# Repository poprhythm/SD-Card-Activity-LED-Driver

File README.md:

# SD-Card-Activity-LED-Driver
Switches on and off an LED based on SD Card activity

Components

- C1:	0.1uF	 SMD 0805
- D1:	LED	SMD 0201
- Q1: [BSS138](https://www.onsemi.com/pub/Collateral/BSS138-D.PDF)
- R1:	2K	SMD 0805
- R2:	330	SMD 0805
- U1:	[74LVC1G04](https://www.ti.com/product/SN74LVC1G04)
- Conn_LDO: AMS1117-3.3V Buck Module LDO

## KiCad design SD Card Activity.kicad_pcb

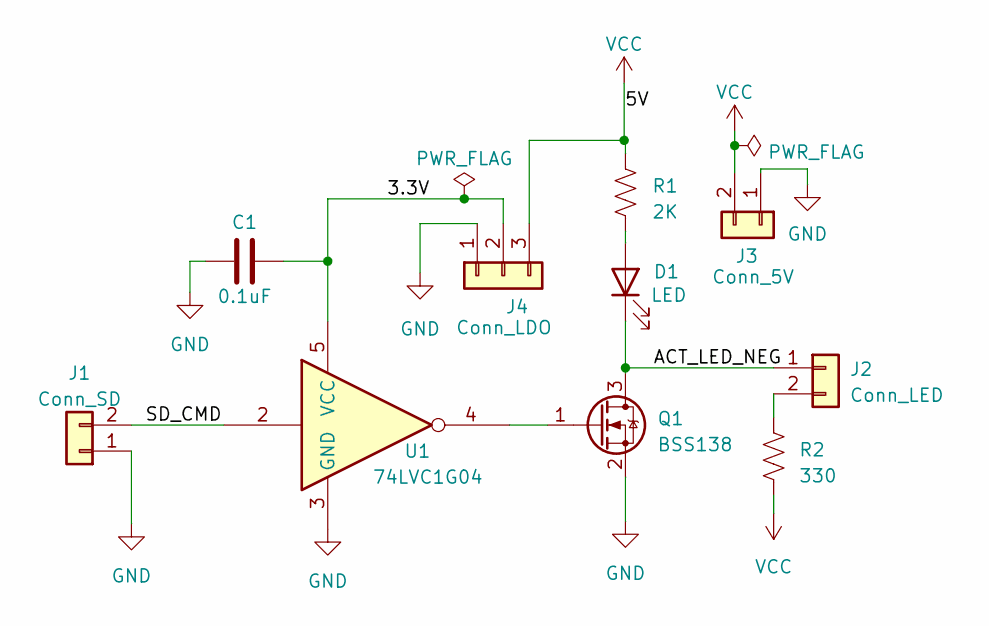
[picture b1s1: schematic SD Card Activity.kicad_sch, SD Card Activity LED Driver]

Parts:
C1: 0.1uF; C_0805_2012Metric_Pad1.18x1.45mm_HandSolder
D1: LED; LED_0201_0603Metric_Pad0.64x0.40mm_HandSolder
J1: Conn_SD; PinSocket_1x02_P2.54mm_Vertical
J2: Conn_LED; PinSocket_1x02_P2.54mm_Vertical
J3: Conn_5V; PinSocket_1x02_P2.54mm_Vertical
J4: Conn_LDO; PinSocket_1x03_P2.54mm_Vertical
Q1: BSS138; SOT-23
R1: 2K; C_0805_2012Metric_Pad1.18x1.45mm_HandSolder
R2: 330; C_0805_2012Metric_Pad1.18x1.45mm_HandSolder
U1: 74LVC1G04; SOT-553

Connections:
/3.3V: C1.1, J4.2, U1.5 (VCC)
/ACT_LED_NEG: D1.1 (K), J2.1, Q1.3 (D)
/SD_CMD: J1.2, U1.2
GND: C1.2, J1.1, J3.1, J4.1, Q1.2 (S), U1.3 (GND)
unnamed: D1.2 (A), R1.2
unnamed: J2.2, R2.1
unnamed: Q1.1 (G), U1.4
VCC: J3.2, J4.3, R1.1, R2.2

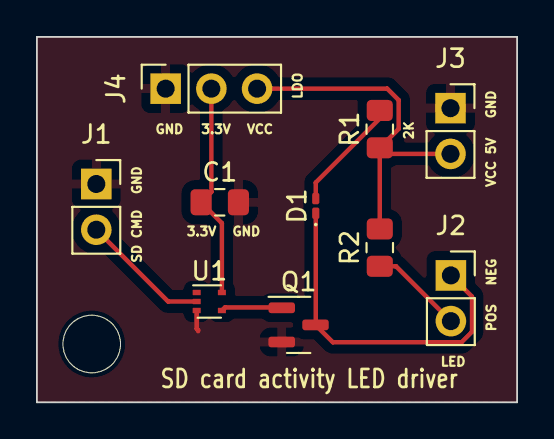
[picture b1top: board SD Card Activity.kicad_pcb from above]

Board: 2 copper layers, 26.7 x 20.3 mm, 10 parts (0 on the bottom side), 8 nets.

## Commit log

2023-07-09 Initial
2023-07-24 Add images
